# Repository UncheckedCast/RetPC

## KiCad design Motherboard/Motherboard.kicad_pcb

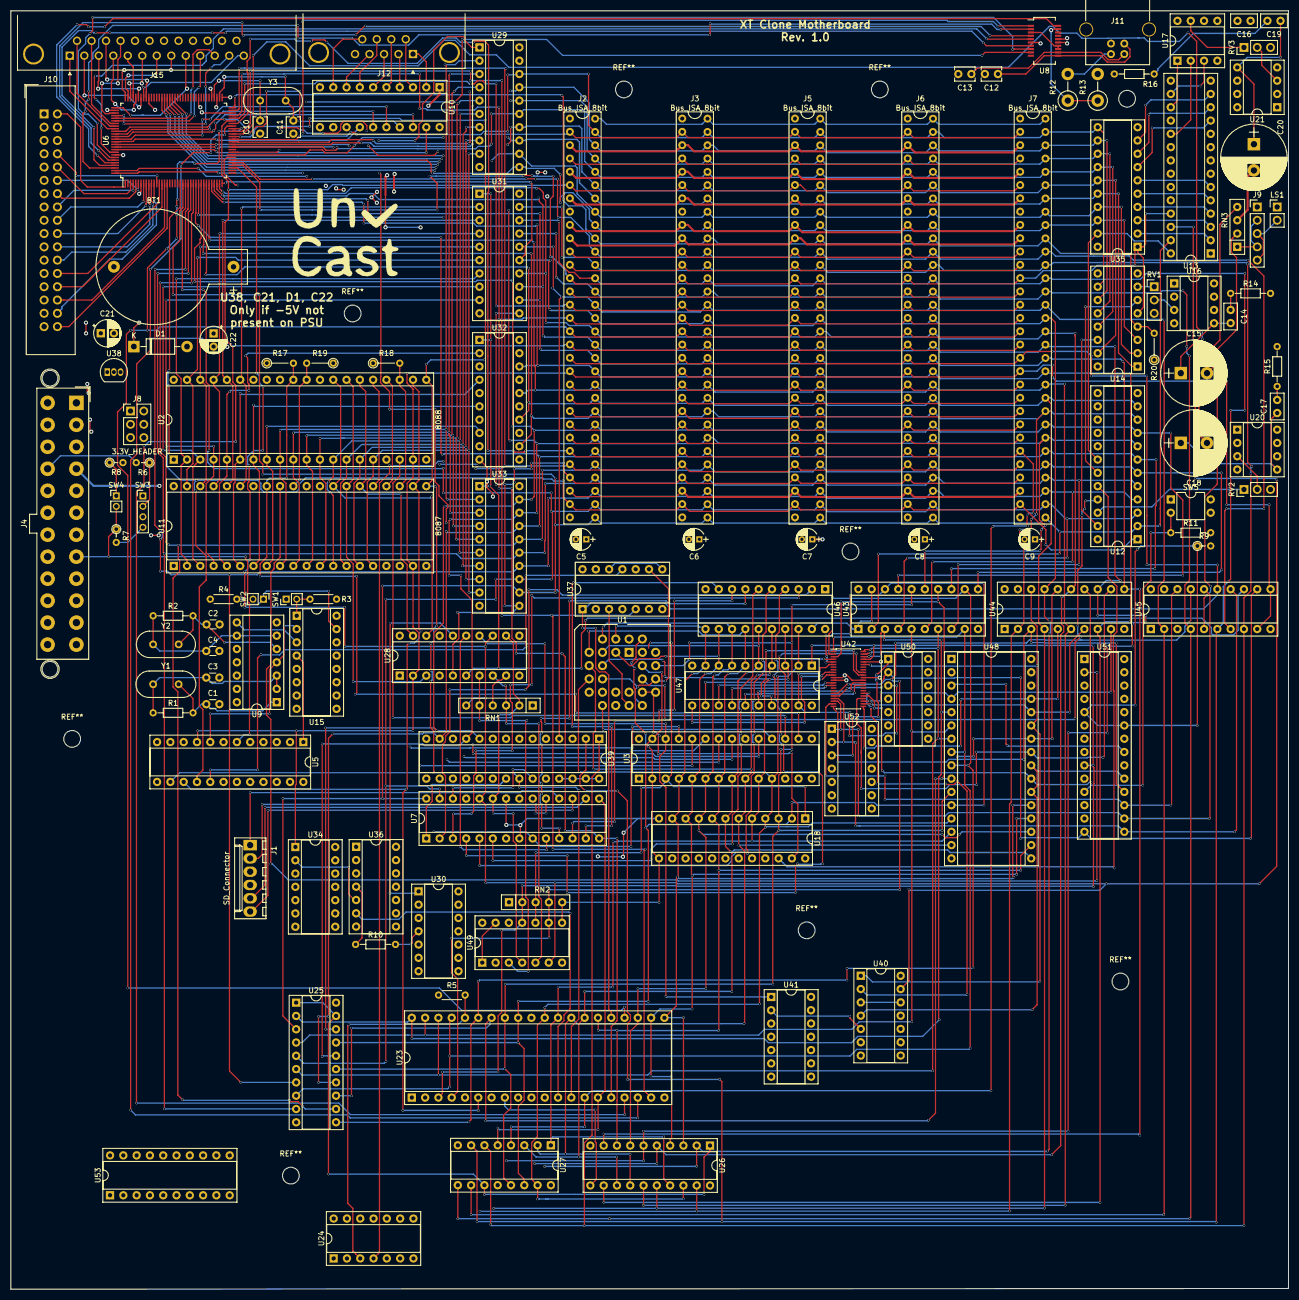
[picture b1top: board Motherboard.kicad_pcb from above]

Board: 4 copper layers, 244.1 x 244.2 mm, 122 parts (0 on the bottom side), 289 nets.

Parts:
BT1: Battery_Cell; CR2032H
C1, C3: 33p; C_Disc_D3.0mm_W1.6mm_P2.50mm
C2, C4: 30p; C_Disc_D3.0mm_W1.6mm_P2.50mm
C5, C6, C7, C8, C9: 1u; CP_Radial_D4.0mm_P2.00mm
C10, C11, C12, C13: C_Small; C_Disc_D3.8mm_W2.6mm_P2.50mm
C14, C17, C19: 50n; C_Disc_D5.0mm_W2.5mm_P2.50mm
C15, C18, C20: 270u; CP_Radial_D12.5mm_P5.00mm
C16: 100n; C_Disc_D5.0mm_W2.5mm_P2.50mm
C21: 22u; CP_Radial_D5.0mm_P2.50mm
C22: 10u; CP_Radial_D5.0mm_P2.50mm
D1: 1N4001; D_DO-41_SOD81_P10.16mm_Horizontal
J1: SD_Connector; Molex_KK-6410-06_06x2.54mm_Straight
J2, J3, J5, J6, J7: Bus_ISA_8bit; ISA-8-bit
J4: ATX24; Molex_MiniFit-JR-5556-24B_2x12x4.20mm_Straight
J8: 3.3V_HEADER; Pin_Header_Straight_2x03_Pitch2.54mm
J9: AudioJack3_SwitchTR; Pin_Header_Straight_1x05_Pitch2.54mm
J10: Conn_02x17_Odd_Even; IDC-Header_2x17_P2.54mm_Vertical
J11: USB_B
J12: DB9_Male; DSUB-9_Male_Horizontal_Pitch2.77x2.84mm_EdgePinOffset4.94mm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
J15: DB25_Female; DSUB-25_Female_Horizontal_Pitch2.77x2.84mm_EdgePinOffset4.9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
LS1: Speaker; Pin_Header_Straight_1x02_Pitch2.54mm
R1, R2: 1M; R_Axial_DIN0204_L3.6mm_D1.6mm_P7.62mm_Horizontal
R3, R4: 10k; R_Axial_DIN0204_L3.6mm_D1.6mm_P5.08mm_Horizontal
R5: 1k; R_Axial_DIN0204_L3.6mm_D1.6mm_P5.08mm_Horizontal
R6, R8, R9: 1k; R_Axial_DIN0204_L3.6mm_D1.6mm_P2.54mm_Vertical
R7: 220; R_Axial_DIN0204_L3.6mm_D1.6mm_P2.54mm_Vertical
R10: 470R; R_Axial_DIN0204_L3.6mm_D1.6mm_P7.62mm_Horizontal
R11: 6k2; R_Axial_DIN0204_L3.6mm_D1.6mm_P7.62mm_Horizontal
R12, R13: R_Small; R_Axial_DIN0411_L9.9mm_D3.6mm_P5.08mm_Vertical
R14, R15, R16: 10; R_Axial_DIN0204_L3.6mm_D1.6mm_P7.62mm_Horizontal
R17, R18, R19: 4k7; R_Axial_DIN0204_L3.6mm_D1.6mm_P5.08mm_Vertical
R20: R_Small; R_Axial_DIN0204_L3.6mm_D1.6mm_P5.08mm_Vertical
RN1: 4.7k; R_Array_SIP6
RN2: 4.7k; R_Array_SIP5
RN3: 470R; R_Array_SIP4
RV1, RV2, RV3: 10k; Pin_Header_Straight_1x03_Pitch2.54mm
SW1: TURBO; Pin_Header_Straight_1x02_Pitch2.00mm
SW2: FREEZE; Pin_Header_Straight_1x02_Pitch2.00mm
SW3: SW_SPST_LED; Pin_Header_Straight_1x04_Pitch2.00mm
SW4: RESET; Pin_Header_Straight_1x02_Pitch2.00mm
SW5: SW_DIP_x01; DIP-4_W7.62mm
U1: 82C54_PLCC; PLCC-28_THT-Socket
U2: 8088; DIP-40_W15.24mm_Socket
U3: 8259; DIP-28_W7.62mm_Socket
U5: ATF750LVC; DIP-24_W7.62mm_Socket
U6: FDC37B787-NS; LQFP-128_14x20mm_Pitch0.5mm
U7, U13: ATmega328-PU; DIP-28_W7.62mm_Socket
U8: FT231XS; SSOP-24_3.9x8.7mm_Pitch0.635mm
U9: 40106; DIP-14_W7.62mm_Socket
U10: GD75232N; DIP-20_W7.62mm_Socket
U11: 8087; DIP-40_W15.24mm_Socket
U12, U18: ATF750LVC-fdc; DIP-24_W7.62mm_Socket
U14: SN76489A-ALT; DIP-16_W7.62mm_Socket
U15: 74LS257; DIP-16_W7.62mm_Socket
U16, U20, U21: LM386; DIP-8_W7.62mm_Socket
U17: MAX538BEPA+; DIP-8_W7.62mm_Socket
U23: 8237; DIP-40_W15.24mm_Socket
U24, U30, U34, U41: 74LS04; DIP-14_W7.62mm_Socket
U25, U32, U43, U44, U45: 74LS244; DIP-20_W7.62mm_Socket
U26: 74LS373; DIP-20_W7.62mm_Socket
U27: 74LS670; DIP-16_W7.62mm_Socket
U28: 8288; DIP-20_W7.62mm_Socket
U29, U35, U46, U47: 74LS245; DIP-20_W7.62mm_Socket
U31, U33: 74LS573; DIP-20_W7.62mm_Socket
U36: 74LS00; DIP-14_W7.62mm_Socket
U37: 74LS74; DIP-14_W7.62mm_Socket
U38: L79L05_TO92; TO-92_Inline
U39, U51: ATF750LVC; DIP-28_W7.62mm_Socket
U40: 74LS27; DIP-14_W7.62mm_Socket
U42: AS6C8008; TSSOP-44_4.4x11.2mm_P0.5mm
U48: SST39SF010; DIP-32_W15.24mm_Socket
U49: 74LS243; DIP-14_W7.62mm_Socket
U50: 7400; DIP-14_W7.62mm_Socket
U52: 74LS32; DIP-14_W7.62mm_Socket
U53: 74LS322; DIP-20_W7.62mm_Socket
Y1: 14.31818 MHz; Crystal_HC49-4H_Vertical
Y2: 24.000 MHz; Crystal_HC49-U_Vertical
Y3: 32.768kHz; Crystal_HC49-U_Vertical

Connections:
+3V3: J4.1, J4.2, J4.12, J4.13, J8.2, J8.4, J8.6, U17.6
+5V: C5.1, C6.1, C7.1, C8.1, C9.1, C16.2, J1.3, J2.3, J2.29, J3.3, J3.29, J4.4, J4.6, J4.21, J4.22, J4.23, J5.3, J5.29, J6.3, J6.29, J7.3, J7.29, R3.1, R4.1, R5.1, R9.2, R11.2, R17.1, R18.1, R19.1, R20.1, RN1.1, RN2.1, U1.13, U1.17, U1.28, U2.40, U3.28, U5.5, U5.24, U6.62, U6.93, U6.121, U7.7, U7.20, U7.21, U8.15, U9.14, U10.20, U11.34, U11.40, U12.24, U13.7, U13.20, U13.21, U14.16, U15.16, U16.6, U17.8, U18.24, U20.6, U21.6, U23.5, U23.31, U25.20, U26.20, U27.16, U28.20, U29.20, U35.20, U37.2, U37.4, U37.10, U37.14, U39.24, U42.11, U42.33, U42.40, U43.20, U47.20, U48.32, U49.14, U51.24
+12V: J2.9, J3.9, J4.10, J4.11, J5.9, J6.9, J7.9, U10.1
-5V: C22.2, D1.2, J2.5, J3.5, J4.20, J5.5, J6.5, J7.5, U38.3
-12V: C21.2, D1.1, J2.7, J3.7, J4.14, J5.7, J6.7, J7.7, U10.10, U38.2
/5V_SB: J4.9, U6.69
/AD0: U2.16, U11.16, U29.9, U33.9
/AD1: U2.15, U11.15, U29.8, U33.8
/AD2: U2.14, U11.14, U29.7, U33.7
/AD3: U2.13, U11.13, U29.6, U33.6
/AD4: U2.12, U11.12, U29.5, U33.5
/AD5: U2.11, U11.11, U29.4, U33.4
/AD6: U2.10, U11.10, U29.3, U33.3
/AD7: U2.9, U11.9, U29.2, U33.2
/AD8: U2.8, U11.8, U32.8
/AD9: U2.7, U11.7, U32.6
/AD10: U2.6, U11.6, U32.4
/AD11: U2.5, U11.5, U32.2
/AD12: U2.4, U11.4, U31.9
/AD13: U2.3, U11.3, U31.8
/AD14: U2.2, U11.2, U31.7
/AD15: U2.39, U11.39, U31.6
/AD16: U2.38, U11.38, U31.5
/AD17: U2.37, U11.37, U31.4
/AD18: U2.36, U11.36, U31.3
/AD19: U2.35, U11.35, U31.2
/AEN: J2.42, J3.42, J5.42, J6.42, J7.42, U6.43, U45.7
/ALE: J2.28, J3.28, J5.28, J6.28, J7.28, U28.5, U31.11, U33.11
/BSY: R18.2, U2.23, U11.23
/DCLK: U23.12, U36.6
/DMA/A0: J2.62, J3.62, J5.62, J6.62, J7.62, U6.23, U7.28, U12.2, U13.27, U25.3, U33.12, U43.2
/DMA/A1: J2.61, J3.61, J5.61, J6.61, J7.61, U6.24, U7.27, U12.3, U25.5, U33.13, U43.4
/DMA/A2: J2.60, J3.60, J5.60, J6.60, J7.60, U6.25, U12.4, U25.7, U33.14, U43.6
/DMA/A3: J2.59, J3.59, J5.59, J6.59, J7.59, U6.26, U12.5, U25.9, U33.15, U43.8
/DMA/A4: J2.58, J3.58, J5.58, J6.58, J7.58, U6.27, U12.6, U25.12, U33.16, U43.11
/DMA/A5: J2.57, J3.57, J5.57, J6.57, J7.57, U6.28, U12.7, U25.14, U33.17, U39.13, U43.13
/DMA/A6: J2.56, J3.56, J5.56, J6.56, J7.56, U6.29, U12.8, U25.16, U33.18, U39.11, U43.15
/DMA/A7: J2.55, J3.55, J5.55, J6.55, J7.55, U6.30, U12.9, U25.18, U33.19, U39.10, U43.17
/DMA/A8: J2.54, J3.54, J5.54, J6.54, J7.54, U6.31, U12.10, U26.19, U32.12, U39.9, U44.2
/DMA/A9: J2.53, J3.53, J5.53, J6.53, J7.53, U6.32, U12.11, U26.16, U32.14, U39.8, U44.4
/DMA/A10: J2.52, J3.52, J5.52, J6.52, J7.52, U6.33, U26.15, U32.16, U44.6
/DMA/A11: J2.51, J3.51, J5.51, J6.51, J7.51, U6.34, U26.12, U32.18, U44.8
/DMA/A12: J2.50, J3.50, J5.50, J6.50, J7.50, U6.35, U26.9, U31.12, U44.11
/DMA/A13: J2.49, J3.49, J5.49, J6.49, J7.49, U6.36, U26.6, U31.13, U39.7, U44.13
/DMA/A14: J2.48, J3.48, J5.48, J6.48, J7.48, U6.37, U26.5, U31.14, U39.6, U44.15
/DMA/A15: J2.47, J3.47, J5.47, J6.47, J7.47, U6.38, U26.2, U31.15, U39.5, U44.17
/DMA/A16: J2.46, J3.46, J5.46, J6.46, J7.46, U27.10, U31.16, U39.4, U45.2
/DMA/A17: J2.45, J3.45, J5.45, J6.45, J7.45, U27.9, U31.17, U39.3, U45.4
/DMA/A18: J2.44, J3.44, J5.44, J6.44, J7.44, U27.7, U31.18, U39.2, U45.6
/DMA/A19: J2.43, J3.43, J5.43, J6.43, J7.43, U27.6, U31.19, U39.1, U45.8
/DMA/XA2: U23.34, U25.13, U42.3, U43.14, U48.10
/DMA/XA3: U23.35, U25.11, U42.2, U43.12, U48.9
/DMA/XA4: U23.37, U25.8, U42.1, U43.9, U48.8
/DMA/~DMAEN: U25.1, U25.19, U26.1, U27.11
/DRQ0: U6.55, U23.19, U37.5
/DRQ1: J2.18, J3.18, J5.18, J6.18, J7.18, U6.57, U23.18
/DRQ2: J2.6, J3.6, U6.59, U23.17
/DRQ3: J2.16, J3.16, J5.16, J6.16, J7.16, U6.61, U7.14, U23.16
/Divisible Clock/OSC_INT: U5.8, U9.4, U15.2
/Divisible Clock/~RES: J4.8, R7.1, SW4.2, U5.6
/FDC-Serial/D0: J2.40, J3.40, J5.40, J6.40, J7.40, U6.44, U7.2, U14.3, U29.11, U35.18, U46.2
/FDC-Serial/D1: J2.39, J3.39, J5.39, J6.39, J7.39, U6.45, U7.3, U14.2, U29.12, U35.17, U46.3
/FDC-Serial/D2: J2.38, J3.38, J5.38, J6.38, J7.38, U6.46, U7.4, U14.1, U29.13, U35.16, U46.4
/FDC-Serial/D3: J2.37, J3.37, J5.37, J6.37, J7.37, U6.47, U7.5, U14.15, U29.14, U35.15, U46.5
/FDC-Serial/D4: J2.36, J3.36, J5.36, J6.36, J7.36, U6.49, U7.6, U14.13, U29.15, U35.14, U46.6
/FDC-Serial/D5: J2.35, J3.35, J5.35, J6.35, J7.35, U6.50, U7.11, U14.12, U29.16, U35.13, U46.7
/FDC-Serial/D6: J2.34, J3.34, J5.34, J6.34, J7.34, U6.51, U7.12, U14.11, U29.17, U35.12, U46.8
/FDC-Serial/D7: J2.33, J3.33, J5.33, J6.33, J7.33, U6.52, U7.13, U14.10, U29.18, U35.11, U46.9
/FDC-Serial/RX1: U6.112, U10.17
/FDC-Serial/TX1: U6.113, U10.15
/FDC-Serial/~CTS1: U6.116, U10.14
/FDC-Serial/~DCD1: U6.119, U10.19
/FDC-Serial/~DSR1: U6.114, U10.18
/FDC-Serial/~DTR1: U6.117, U10.13
/FDC-Serial/~RI1: U6.118, U10.12
/FDC-Serial/~RTS1: U6.115, U10.16
/HDD Controller/ADDR: U7.26, U39.23
/HDD Controller/MISO: J1.1, U7.18
/HDD Controller/MOSI: J1.6, U7.17
/HDD Controller/SCK: J1.2, U7.19
/HDD Controller/SS-CS: J1.5, U7.16
/HDD Controller/~RESET: U7.1, U39.21
/HLDA: R19.2, U2.30, U11.31
/INTR: U2.18, U3.17
/IO-Decoder/AENBRD: U28.6, U31.1, U32.1, U33.1, U45.13
/IO-Decoder/DT_~R: U28.4, U29.1
/IO-Decoder/IO_SigDecoder/IOCHCK_I: R9.1, U51.5
/IO-Decoder/ROMADDR: U40.4, U48.22, U48.24, U51.19
/IO-Decoder/XA10: U42.27, U44.14, U48.23
/IO-Decoder/XA11: U42.26, U44.12, U48.25
/IO-Decoder/XA12: U42.25, U44.9, U48.4
/IO-Decoder/XA13: U42.24, U44.7, U48.28
/IO-Decoder/XA14: U42.23, U44.5, U48.29
/IO-Decoder/XA15: U42.22, U44.3, U51.18
/IO-Decoder/XA16: U42.21, U45.18, U51.17
/IO-Decoder/XA17: U42.20, U45.16, U51.16, U52.1
/IO-Decoder/XA18: U42.19, U45.14, U51.15, U52.2
/IO-Decoder/XA19: U42.18, U45.12, U50.2, U51.14
/IO-Decoder/~CS6: U48.3, U51.21
/IO-Decoder/~DEN: U29.19, U30.2
/IO-Decoder/~MEMW: RN1.3, U28.8, U49.5
/IO-Decoder/~MWTC: RN1.4, U28.9
/IO-Decoder/~RAMSEL: U42.6, U47.19, U50.3
/IO_READY: J2.41, J3.41, J5.41, J6.41, J7.41, R20.2, U6.64, U14.4
/IRQ0: U1.12, U3.18
/IRQ1: U3.19, U6.83
/IRQ3: U3.21, U6.84
/IRQ4: U3.22, U6.85
/IRQ5: U3.23, U6.86, U7.9
/IRQ6: U3.24, U6.87
/IRQ7: U3.25, U6.88
/ISA/IOCHCK: J2.32, J3.32, J5.32, J6.32, J7.32
/ISA/IRQ2: J2.4, J3.4
/ISA/IRQ3: J2.25, J3.25, J5.25, J6.25, J7.25
/ISA/IRQ4: J2.24, J3.24, J5.24, J6.24, J7.24
/ISA/IRQ5: J2.23, J3.23, J5.23, J6.23, J7.23
/ISA/IRQ6: J2.22, J3.22, J5.22, J6.22, J7.22
/ISA/IRQ7: J2.21, J3.21, J5.21, J6.21, J7.21
/ISA/~IOR: J2.14, J3.14, J5.14, J6.14, J7.14
/MIDI/DACCS: U13.16, U17.3
/MIDI/DIN: U13.17, U17.1
/MIDI/MIDIS_OUT: C20.2, RN3.3
/MIDI/SCLK: U13.19, U17.2
/MIDI/SPEAKER: RV2.1, U12.22
/MIDI/SPKR: C18.2, RN3.4
/MIDI/TANDY: C15.2, RN3.2
/MIDI/~PORT33X: U12.18, U13.28, U35.19
/MIDI/~TANDY_SEL: U12.19, U14.6
/MIDI/~~4MHZ: U12.23, U14.14
/N.P.NPI: U11.32, U51.2
/OSC: J2.30, J3.30, J5.30, J6.30, J7.30, U5.16, U6.22, U12.1
/PCLK: U5.17, U37.11
/PU: R17.2, U2.31, U3.16, U11.33
/QS0: U2.25, U11.25
/QS1: U2.24, U11.24
/READY: U2.22, U5.15, U11.22, U23.6
/RESET: J2.2, J3.2, J5.2, J6.2, J7.2, U2.21, U5.14, U6.53, U11.21, U23.13, U39.22
/SPEAKER: U1.20, U12.21
/SPKR_DATA: U12.20, U18.22
/SYS_CLK: J2.20, J3.20, J5.20, J6.20, J7.20, U2.19, U5.9, U11.19, U28.2, U34.1, U45.9, U45.11
/TC: J2.27, J3.27, J5.27, J6.27, J7.27, U6.63, U24.4
/XA0: U1.22, U3.27, U18.2, U23.32, U25.17, U27.14, U42.5, U43.18, U48.12
/XA1: U1.23, U18.3, U23.33, U25.15, U27.13, U42.4, U43.16, U48.11
/XA5: U23.38, U25.6, U42.44, U43.7, U48.7
/XA6: U23.39, U25.4, U42.43, U43.5, U48.6
/XA7: U23.40, U25.2, U42.42, U43.3, U48.5
/XA8: U40.1, U42.39, U44.18, U48.27
/XA9: U40.2, U42.28, U44.16, U48.26
/XD0: U1.9, U3.11, U18.4, U23.30, U26.18, U27.15, U46.18, U47.2, U48.13
/XD1: U1.8, U3.10, U18.5, U23.29, U26.17, U27.1, U46.17, U47.3, U48.14
/XD2: U1.7, U3.9, U18.6, U23.28, U26.14, U27.2, U46.16, U47.4, U48.15
/XD3: U1.6, U3.8, U18.7, U23.27, U26.13, U27.3, U46.15, U47.5, U48.17
/XD4: U1.5, U3.7, U18.8, U23.26, U26.8, U46.14, U47.6, U48.18
/XD5: U1.4, U3.6, U18.9, U23.23, U26.7, U46.13, U47.7, U48.19
/XD6: U1.3, U3.5, U18.10, U23.22, U26.4, U46.12, U47.8, U48.20
/XD7: U1.2, U3.4, U18.11, U23.21, U26.3, U46.11, U47.9, U48.21
/~AEN: U7.10, U28.15
/~DACK0: U6.54, U45.5
/~DACK0BRD: J2.19, J3.19, J5.19, J6.19, J7.19, U23.25, U37.1, U45.15
/~DACK1: J2.17, J3.17, J5.17, J6.17, J7.17, U6.56, U23.24
/~DACK2: J2.26, J3.26, J5.26, J6.26, J7.26, U6.58, U23.14, U27.4
/~DACK3: J2.15, J3.15, J5.15, J6.15, J7.15, U6.60, U7.15, U23.15, U27.5
/~DMAEN: U49.1, U49.13
/~INTA: U3.26, U28.14, U41.1
/~IOR: RN1.6, U6.41, U7.24, U13.26, U28.13, U40.13, U49.6
/~IOW: J2.13, J3.13, J5.13, J6.13, J7.13, RN1.2, U6.42, U7.23, U13.25, U14.5, U28.12, U35.1, U49.4
/~MEMR: J2.12, J3.12, J5.12, J6.12, J7.12, RN1.5, U28.7, U49.3
/~MEMW: J2.11, J3.11, J5.11, J6.11, J7.11
/~S0: U2.26, U11.26, U28.19
/~S1: U2.27, U11.27, U28.3
/~S2: U2.28, U11.28, U28.18
/~XIOR: RN2.5, U1.26, U3.2, U18.13, U49.8
/~XIOW: RN2.3, U1.27, U3.3, U18.1, U49.10
/~XMEMR: RN2.2, U23.3, U42.41, U47.1, U49.11, U51.9
/~XMEMW: RN2.4, U23.4, U42.17, U45.17, U49.9
GND: BT1.2, C1.2, C2.2, C3.2, C4.2, C5.2, C6.2, C7.2, C8.2, C9.2, C10.1, C11.1, C12.2, C13.2, C16.1, C21.1, C22.1, J1.4, J2.1, J2.10, J2.31, J3.1, J3.10, J3.31, J4.3, J4.5, J4.7, J4.15, J4.17, J4.18, J4.19, J4.24, J5.1, J5.10, J5.31, J6.1, J6.10, J6.31, J7.1, J7.10, J7.31, J8.1, J8.3, J8.5, J9.1, J10.1, J10.3, J10.5, J10.7, J10.9, J10.11, J10.13, J10.15, J10.17, J10.19, J10.21, J10.23, J10.25, J10.27, J10.29, J10.31, J10.33, J11.4, J11.5, J12.5, J15.18, J15.19, J15.20, J15.21, J15.22, J15.23, J15.24, J15.25, LS1.1, R8.2, R13.2, R14.2, R15.2, R16.2, RV1.3, RV2.3, RV3.3, SW1.1, SW2.2, SW3.1, SW3.3, SW5.1, U1.14, U2.1, U2.20, U2.33, U3.14, U5.4, U5.7, U5.12, U6.7, U6.48, U6.67, U6.74, U6.104, U7.8, U7.22, U8.6, U8.16, U9.7, U10.11, U11.1, U11.20, U12.12, U13.8, U13.22, U14.8, U15.8, U16.2, U16.4, U17.5, U18.12, U20.2, U20.4, U21.2, U21.4, U23.20, U25.10, U26.10, U27.8, U28.1, U28.10, U29.10, U31.10, U32.10, U33.10, U35.10, U37.7, U38.1, U39.12, U42.12, U42.34, U43.10, U44.1, U44.19, U45.1, U45.19, U47.10, U48.2, U48.16, U48.31, U49.7, U51.12
unnamed: BT1.1, U6.65
unnamed: C1.1, R1.2, U9.1, Y1.2
unnamed: C2.1, R2.2, U9.5, Y2.2
unnamed: C3.1, R1.1, U9.2, U9.3, Y1.1
unnamed: C4.1, R2.1, U9.6, U9.9, Y2.1
unnamed: C10.2, U6.68, Y3.1
unnamed: C11.2, U6.66, Y3.2
unnamed: C12.1, J11.3, U8.11
unnamed: C13.1, J11.2, U8.12
unnamed: C14.1, C15.1, U16.5
unnamed: C14.2, R14.1
unnamed: C17.1, C18.1, U20.5
unnamed: C17.2, R15.1
unnamed: C19.1, C20.1, U21.5
unnamed: C19.2, R16.1
unnamed: J4.16, R6.2
unnamed: J9.2, J9.4, RN3.1
unnamed: J9.3, J9.5, LS1.2
unnamed: J10.2, U6.1
unnamed: J10.8, U6.13
unnamed: J10.10, U6.3
unnamed: J10.12, U6.6
unnamed: J10.14, U6.5
unnamed: J10.16, U6.4
unnamed: J10.18, U6.8
unnamed: J10.20, U6.9
unnamed: J10.22, U6.10
unnamed: J10.24, U6.11
unnamed: J10.26, U6.14
unnamed: J10.28, U6.15
unnamed: J10.30, U6.16
unnamed: J10.32, U6.12
unnamed: J10.34, U6.17
unnamed: J11.1, R12.2
unnamed: J12.1, U10.2
unnamed: J12.2, U10.4
unnamed: J12.3, U10.6
unnamed: J12.4, U10.8
unnamed: J12.6, U10.3
unnamed: J12.7, U10.5
unnamed: J12.8, U10.7
unnamed: J12.9, U10.9
unnamed: J15.1, U6.111
unnamed: J15.2, U6.96
unnamed: J15.3, U6.97
unnamed: J15.4, U6.98
unnamed: J15.5, U6.99
unnamed: J15.6, U6.100
unnamed: J15.7, U6.101
unnamed: J15.8, U6.102
unnamed: J15.9, U6.103
unnamed: J15.10, U6.108
unnamed: J15.11, U6.107
unnamed: J15.12, U6.106
unnamed: J15.13, U6.95
unnamed: J15.14, U6.110
unnamed: J15.15, U6.109
unnamed: J15.16, U6.94
unnamed: J15.17, U6.105
unnamed: R3.2, SW1.2, U15.1
unnamed: R4.2, SW2.1, U15.15
unnamed: R5.2, U23.36, U24.3
unnamed: R6.1, SW3.2
unnamed: R7.2, SW3.4
unnamed: R8.1, SW4.1
unnamed: R10.1, U36.4
unnamed: R10.2, U30.4
unnamed: R11.1, SW5.2, U51.11
unnamed: R12.1, R13.1, U8.19
unnamed: RV1.1, U14.7
unnamed: RV1.2, U16.3
unnamed: RV2.2, U20.3
unnamed: RV3.1, U17.7
unnamed: RV3.2, U21.3
unnamed: U1.10, U1.18, U1.21, U37.9
unnamed: U1.16, U37.3
unnamed: U1.19, U18.23
unnamed: U6.120, U8.5
unnamed: U6.122, U8.8
unnamed: U6.123, U8.4
unnamed: U6.124, U8.20
unnamed: U6.125, U8.7
unnamed: U6.126, U8.2
unnamed: U6.127, U8.9
unnamed: U6.128, U8.1
unnamed: U8.3, U8.13, U8.14
unnamed: U13.2, U35.2
unnamed: U13.3, U35.3
unnamed: U13.4, U35.4
unnamed: U13.5, U35.5
unnamed: U13.6, U35.6
unnamed: U13.11, U35.7
unnamed: U13.12, U35.8
unnamed: U13.13, U35.9
unnamed: U9.8, U15.3
unnamed: U5.1, U15.4
unnamed: U23.8, U26.11
unnamed: U28.16, U30.1
unnamed: U34.2, U36.5
unnamed: U37.8, U37.12
unnamed: U40.5, U41.2
unnamed: U40.6, U46.1
unnamed: U40.3, U40.12
unnamed: U42.9, U47.11
unnamed: U42.10, U47.12
unnamed: U42.13, U47.13
unnamed: U42.14, U47.14
unnamed: U42.31, U47.15
unnamed: U42.32, U47.16
unnamed: U42.35, U47.17
unnamed: U42.36, U47.18
unnamed: U43.1, U43.19, U46.19
unnamed: U50.1, U52.3

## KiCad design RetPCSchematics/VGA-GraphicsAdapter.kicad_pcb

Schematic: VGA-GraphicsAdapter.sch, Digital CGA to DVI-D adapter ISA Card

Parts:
C1, C2, C3, C4, C5, C6, C7, C10: C; CP_Radial_D4.0mm_P1.50mm
H1, H2: MountingHole; MountingHole_2.2mm_M2
J1: Bus_ISA_8bit; 8Bit_ISA_BUS
J2: 74320-9004; DVI_Female_74320-9004; MPN 74320-9004; Digi-Key_PN WM6095-ND
J3: Conn_01x03_Male; PinHeader_1x03_P1.00mm_Vertical
R1: 220R
R2: 370R
RN1: R_Network08; R_Array_SIP9
U1: LM317T; TO-220-3; MPN LM317T; Digi-Key_PN 497-1575-5-ND
U3, U4, U6, U21: ATF22V10D; DIP-24_W7.62mm_Socket
U5, U8, U12: 74LS245; DIP-20_W7.62mm_Socket
U7, U9, U22: 74LS245A; DIP-20_W7.62mm_Socket
U10: ATmega644P-20PU; DIP-40_W15.24mm
U11: IS61LV5128AL-10TLI; TSSOP-44_4.4x11.2mm_P0.5mm
U13: SN74LVC245AN; DIP-20_W7.62mm_Socket; MPN SN74LVC245AN; Digi-Key_PN 296-8503-5-ND
U36: TFP410; HQFP-64_10x10mm_Pitch0.5mm_handsoldering
U37: ATF750C; DIP-24_W7.62mm_Socket
X1: DGOF5S3; Oscillator_DIP-14

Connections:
(inv)LE: U5.1, U8.1, U11.37 (OE(inv)), U37.21 (IO21)
+3V3: C1.2, C2.2, C3.2, C4.2, C5.2, C6.2, C7.2, C10.2, J3.2, U3.24 (VCC), U4.24 (VCC), U5.20, U6.24 (VCC), U7.20, U8.20, U9.20, U10.10 (VCC), U10.30 (AVCC), U11.11 (VDD), U11.33 (VDD), U12.20, U13.20, U21.24 (VCC), U22.20, U36.1, U36.3, U36.12, U36.15, U36.18, U36.23, U36.29, U36.33, U37.24 (VCC)
+FEMV: J1.3 (VCC), J2.14, X1.14
/A0: J1.62 (BA00), U9.2, U21.13 (IN13)
/A1: J1.61 (BA01), U9.3, U21.14 (IO14)
/A2: J1.60 (BA02), U9.4, U21.15 (IO15)
/A3: J1.59 (BA03), U9.5, U21.16 (IO16)
/A4: J1.58 (BA04), U9.6, U21.17 (IO17)
/A5: J1.57 (BA05), U9.7, U21.18 (IO18)
/A6: J1.56 (BA06), U9.8, U21.19 (IO19)
/A7: J1.55 (BA07), U9.9, U21.20 (IO20)
/A8: J1.54 (BA08), U7.2, U21.21 (IO21)
/A9: J1.53 (BA09), U7.3, U21.11 (IN11)
/A10: J1.52 (BA10), U7.4, U21.10 (IN10)
/A11: J1.51 (BA11), U7.5, U21.9 (IN9)
/A12: J1.50 (BA12), U7.6, U21.8 (IN8)
/A13: J1.49 (BA13), U7.7, U21.7 (IN7)
/A14: J1.48 (BA14), U7.8, U21.6 (IN6)
/A15: J1.47 (BA15), U7.9, U21.5 (IN5)
/D0: U11.9 (IO/0), U12.18, U13.9
/D1: U11.10 (IO/1), U12.17, U13.8
/D2: U11.13 (IO/2), U12.16, U13.7
/D3: U11.14 (IO/3), U12.15, U13.6
/D4: U11.31 (IO/4), U12.14, U13.5
/D5: U11.32 (IO/5), U12.13, U13.4
/D6: U11.36 (IO/7), U12.12, U13.3
/D7: U11.35 (IO/6), U12.11, U13.2
/VA0: U3.14 (IO14), U4.10 (IN10), U8.18, U11.3 (A0)
/VA1: U3.15 (IO15), U4.9 (IN9), U8.17, U11.4 (A1)
/VA2: U3.16 (IO16), U4.8 (IN8), U8.16, U11.5 (A2)
/VA3: U3.17 (IO17), U4.7 (IN7), U8.15, U11.6 (A3)
/VA4: U3.18 (IO18), U4.6 (IN6), U8.14, U11.7 (A4)
/VA5: U3.19 (IO19), U4.5 (IN5), U8.13, U11.16 (A5)
/VA6: U3.20 (IO20), U4.4 (PD/IN4), U8.12, U11.17 (A6)
/VA7: U3.21 (IO21), U4.3 (IN3), U8.11, U11.18 (A7)
/VA8: U3.22 (IO22), U4.2 (IN2), U5.18, U11.19 (A8)
/VA9: U3.23 (IO23), U4.1 (CLK/IN1), U5.17, U11.20 (A9)
/VA10: U4.14 (IO14), U5.16, U11.26 (A10)
/VA11: U4.15 (IO15), U5.15, U11.27 (A11)
/VA12: U4.16 (IO16), U5.14, U11.28 (A12)
/VA13: U4.17 (IO17), U5.13, U11.29 (A13)
/VA14: U4.18 (IO18), U5.12, U11.30 (A14)
/VA15: U4.19 (IO19), U5.11, U11.38 (A15)
/VA16: U4.20 (IO20), U6.18 (IO18), U11.39 (A16)
/VA17: U4.21 (IO21), U6.17 (IO17), U11.40 (A17)
/VA18: U4.22 (IO22), U6.19 (IO19), U11.41 (A18)
/XA0: U8.2, U9.18, U10.23 (PC1)
/XA1: U8.3, U9.17, U10.22 (PC0)
/XA2: U8.4, U9.16, U10.8 (PB7)
/XA3: U8.5, U9.15, U10.7 (PB6)
/XA4: U8.6, U9.14, U10.6 (PB5)
/XA5: U8.7, U9.13, U10.5 (PB4)
/XA6: U8.8, U9.12, U10.4 (PB3)
/XA7: U8.9, U9.11, U10.3 (PB2)
/XA8: U5.2, U7.18, U10.2 (PB1)
/XA9: U5.3, U7.17, U10.1 (PB0)
/XA10: U5.4, U7.16, U10.40 (PA0)
/XA11: U5.5, U7.15, U10.39 (PA1)
/XA12: U5.6, U7.14, U10.38 (PA2)
/XA13: U5.7, U7.13, U10.37 (PA3)
/XA14: U5.8, U7.12, U10.36 (PA4)
/XA15: U5.9, U7.11, U10.35 (PA5)
/XA16: U6.7 (IN7), U10.34 (PA6)
/XA17: U6.8 (IN8), U10.33 (PA7)
/XA18: U6.6 (IN6), U10.24 (PC2)
AEN: J1.42 (AEN), U37.3 (IN3)
ALEN: J1.28 (ALE), U7.1, U9.1, U37.7 (IN7)
ALEN(inv): U7.19, U9.19, U37.19 (IO19)
DE: U36.2, U37.16 (IO16)
Dir: U10.26 (PC4), U22.1
GClock: U6.14 (IO14), U36.57, U37.1 (CLK/IN1)
GEnd: U4.23 (IO23), U37.6 (IN6)
GEnd(inv): U12.19, U37.18 (IO18)
Hsync: U36.4, U37.15 (IO15)
IOR: J1.14 (~IOR), U37.4 (PD/IN4)
IOW: J1.13 (~IOW), U37.2 (IN2)
LoadEnable: U6.3 (IN3), U10.28 (PC6), U11.15 (WE(inv)), U13.19, U37.9 (IN9)
MemW: J1.11 (~MEM), U37.5 (IN5)
unnamed: J1.33 (DB7), U22.9
unnamed: J1.34 (DB6), U22.8
unnamed: J1.35 (DB5), U22.7
unnamed: J1.36 (DB4), U22.6
unnamed: J1.37 (DB3), U22.5
unnamed: J1.38 (DB2), U22.4
unnamed: J1.39 (DB1), U22.3
unnamed: J1.40 (DB0), U22.2
unnamed: J1.43 (BA19), U21.1 (CLK/IN1)
unnamed: J1.44 (BA18), U21.2 (IN2)
unnamed: J1.45 (BA17), U21.3 (IN3)
unnamed: J1.46 (BA16), U21.4 (PD/IN4)
unnamed: RN1.2, U12.2, U36.36, U36.40
unnamed: RN1.3, U12.3, U36.37, U36.41
unnamed: RN1.4, U12.4, U36.38, U36.42
unnamed: RN1.5, U12.5, U36.44, U36.50
unnamed: RN1.6, U12.6, U36.45, U36.51
unnamed: RN1.7, U12.7, U36.46, U36.52
unnamed: RN1.8, U12.8, U36.54, U36.60
unnamed: RN1.9, U12.9, U36.55, U36.61
unnamed: U3.1 (CLK/IN1), U6.16 (IO16)
unnamed: U6.1 (CLK/IN1), X1.8
unnamed: U10.14 (PD0), U13.11, U22.18
unnamed: U10.15 (PD1), U13.12, U22.17
unnamed: U10.16 (PD2), U13.13, U22.16
unnamed: U10.17 (PD3), U13.14, U22.15
unnamed: U10.18 (PD4), U13.15, U22.14
unnamed: U10.19 (PD5), U13.16, U22.13
unnamed: U10.20 (PD6), U13.17, U22.12
unnamed: U10.21 (PD7), U13.18, U22.11
OP: U6.2 (IN2), U10.27 (PC5)
RST: J1.2 (RESET), U37.8 (IN8)
RST(inv): U10.9 (~RESET), U37.20 (IO20)
Sel: U10.25 (PC3), U21.23 (IO23), U22.19
TX0+: J2.18, U36.25
TX0-: J2.17, U36.24
TX1+: J2.10, U36.28
TX1-: J2.9, U36.27
TX2+: J2.2, U36.31
TX2-: J2.1, U36.30
TXC+: J2.23, U36.22
TXC-: J2.24, U36.21
Vsync: U36.5, U37.14 (IO14)
busr: U10.29 (PC7), U37.17 (IO17)

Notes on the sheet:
~~3.35V

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
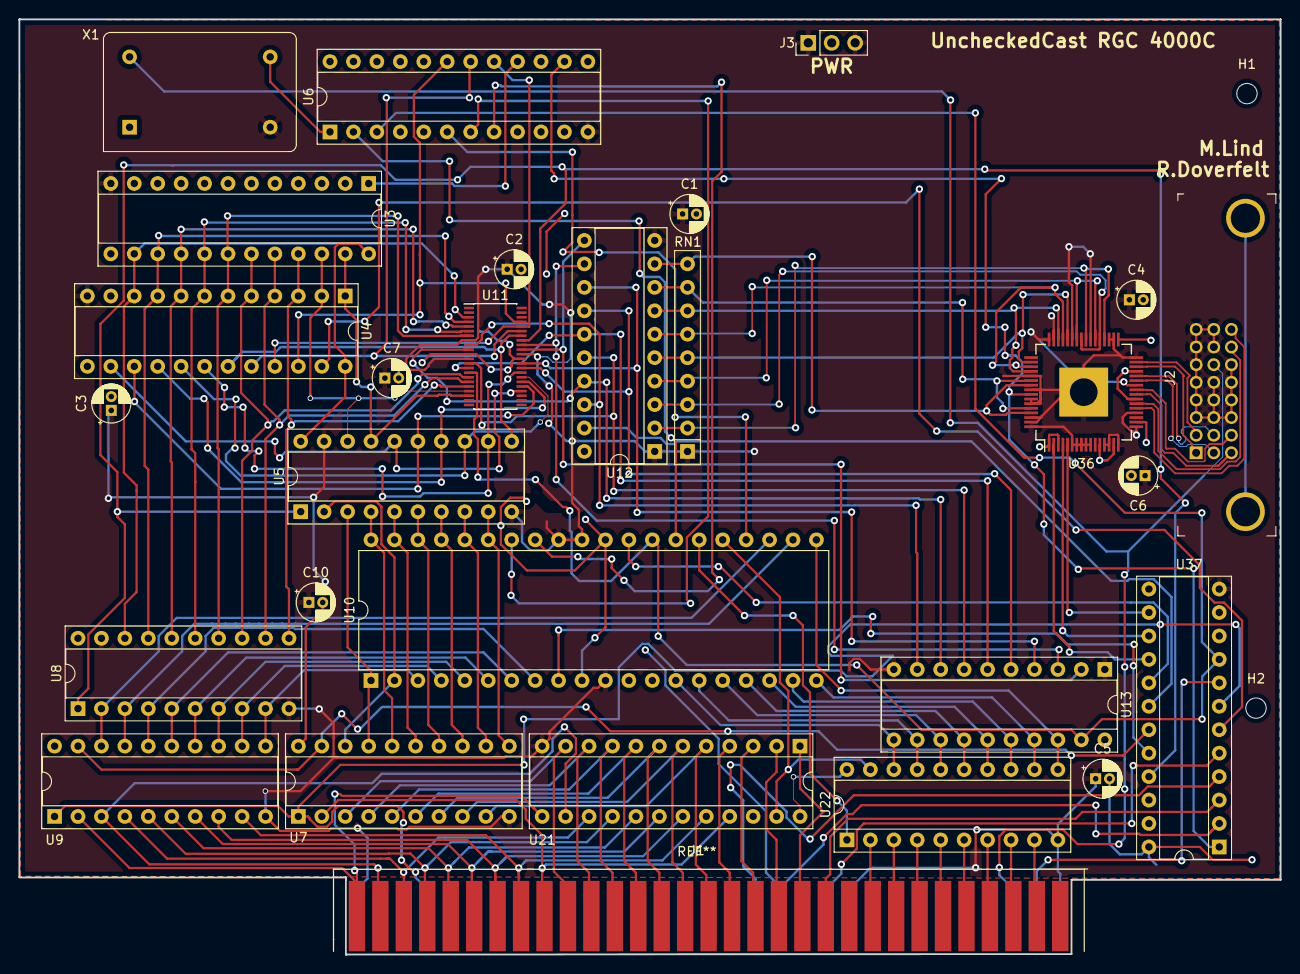
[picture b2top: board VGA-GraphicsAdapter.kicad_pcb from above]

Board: 2 copper layers, 136.7 x 101.3 mm, 30 parts (0 on the bottom side), 123 nets.

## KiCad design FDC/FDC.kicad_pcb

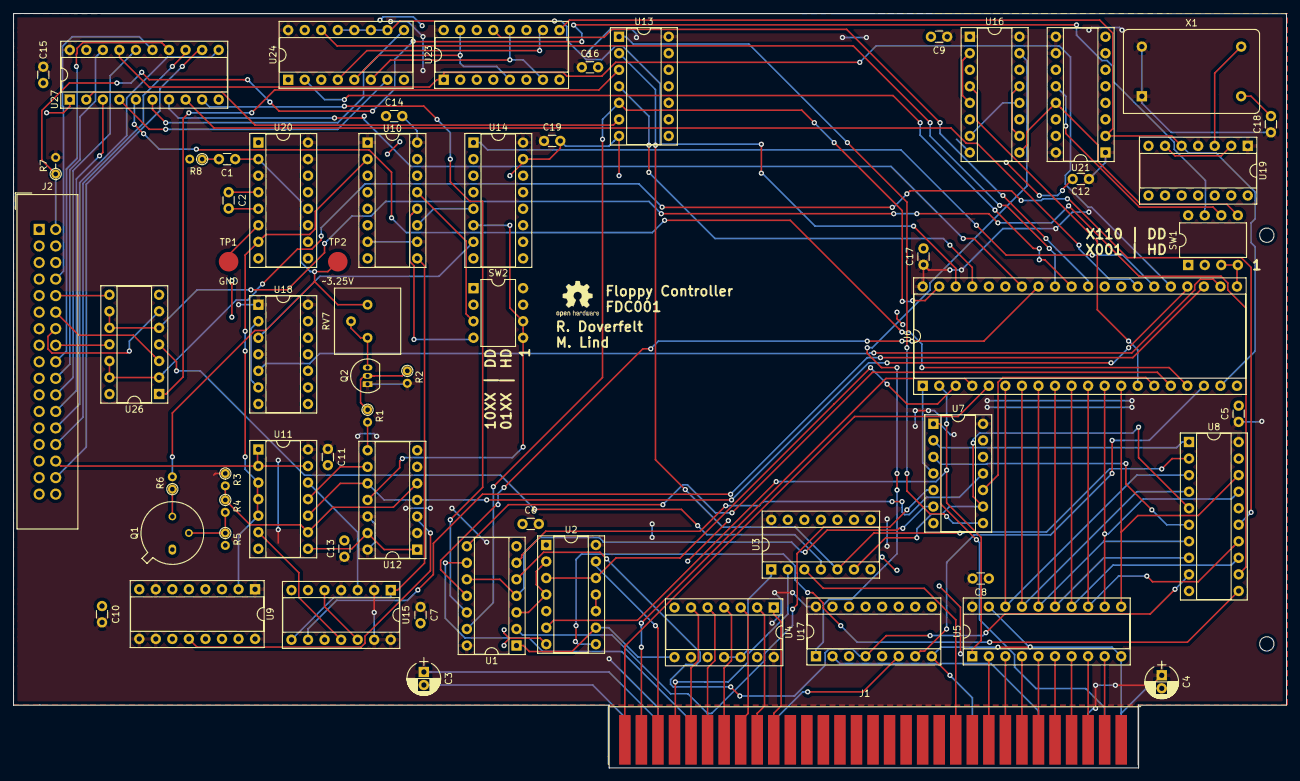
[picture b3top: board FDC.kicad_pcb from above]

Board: 2 copper layers, 195.4 x 115.8 mm, 62 parts (0 on the bottom side), 128 nets.

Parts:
C1: 100p; C_Disc_D3.0mm_W1.6mm_P2.50mm
C2: 33p; C_Disc_D3.0mm_W1.6mm_P2.50mm
C3, C4: 8u2; CP_Radial_D5.0mm_P2.00mm
C5, C6, C7, C8, C9, C10, C11, C12, C13, C14, C15, C16, C17, C18, C19: 4n7; C_Disc_D3.0mm_W1.6mm_P2.50mm
J1: Bus_ISA_8bit; 8Bit_ISA_BUS
J2: Floppy IDC; IDC-Header_2x17_P2.54mm_Vertical
Q1: 2N2219; TO-39-3
Q2: 2N3905; TO-92_Inline_Narrow_Oval
R1: 2k2; R_Axial_DIN0204_L3.6mm_D1.6mm_P1.90mm_Vertical
R2, R3, R5: 1k; R_Axial_DIN0204_L3.6mm_D1.6mm_P1.90mm_Vertical
R4: 1k5; R_Axial_DIN0204_L3.6mm_D1.6mm_P1.90mm_Vertical
R6: 33k; R_Axial_DIN0204_L3.6mm_D1.6mm_P1.90mm_Vertical
R7: 4k7; R_Axial_DIN0204_L3.6mm_D1.6mm_P2.54mm_Vertical
R8: 330R; R_Axial_DIN0204_L3.6mm_D1.6mm_P1.90mm_Vertical
RV7: 20k; 3386P
SW1, SW2: DSEL; DIP-8_W7.62mm
TP1: GND; Measurement_Point_Round-SMD-Pad_Big
TP2: ~~3.25V; Measurement_Point_Round-SMD-Pad_Big
U1, U13: 74LS08; DIP-14_W7.62mm_Socket
U2: 74LS32; DIP-14_W7.62mm_Socket
U3: 74LS02; DIP-14_W7.62mm_Socket
U4: 74LS30; DIP-14_W7.62mm_Socket
U5: 74LS245; DIP-20_W7.62mm_Socket
U6: uPD765BC; DIP-40_W15.24mm_Socket
U7: 74LS04; DIP-14_W7.62mm_Socket
U8: 74LS273; DIP-20_W7.62mm_Socket
U9, U10, U21: 74LS161; DIP-16_W7.62mm_Socket
U11: 74LS10; DIP-14_W7.62mm_Socket
U12, U15, U18, U19: 74LS74; DIP-14_W7.62mm_Socket
U14: 74LS157; DIP-16_W7.62mm_Socket
U16, U23: 74LS175; DIP-16_W7.62mm_Socket
U17: MC3487N; DIP-16_W7.62mm_Socket
U20: 74LS629; DIP-16_W7.62mm_Socket
U24: 74LS153; DIP-16_W7.62mm_Socket
U26: 74LS38; DIP-14_W7.62mm_Socket
U27: 74HC240; DIP-20_W7.62mm_Socket
X1: 16MHZ; Oscillator_DIP-14

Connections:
+5V: C3.1, C4.1, C5.1, C6.2, C7.1, C8.2, C9.1, C10.2, C11.1, C12.2, C13.1, C14.2, C15.1, C16.1, C17.1, C18.1, C19.1, J1.3, J1.29, Q2.1, R2.2, R3.1, R7.2, U1.14, U2.14, U3.14, U4.14, U5.20, U6.40, U7.14, U8.20, U9.1, U9.7, U9.9, U9.10, U9.16, U10.1, U10.7, U10.10, U10.16, U11.14, U12.2, U12.12, U12.14, U13.14, U14.16, U15.2, U15.4, U15.10, U15.13, U15.14, U16.1, U16.16, U17.16, U18.1, U18.4, U18.14, U19.1, U19.4, U20.3, U20.15, U20.16, U21.1, U21.7, U21.9, U21.10, U21.16, U23.16, U24.16, U27.20, X1.1, X1.14
/1MHZ: SW1.6, U21.12
/2MHZ: SW1.5, U16.9, U21.13
/8MHZ: U6.19, U19.5, U21.2, U23.9
/A0: J1.62, U6.5
/A1: J1.61, U6.4
/A2: J1.60, U2.13
/ADDR: U1.1, U2.9, U4.8
/AEN: J1.42, U3.3
/D0: U5.18, U6.6, U8.3
/D1: U5.17, U6.7, U8.4
/D2: U5.16, U6.8, U8.7
/D3: U5.15, U6.9, U8.8
/D4: U5.14, U6.10, U8.13
/D5: U5.13, U6.11, U8.14
/D6: U5.12, U6.12, U8.17
/D7: U5.11, U6.13, U8.18
/DB0: J1.40, U5.2
/DB1: J1.39, U5.3
/DB2: J1.38, U5.4
/DB3: J1.37, U5.5
/DB4: J1.36, U5.6
/DB5: J1.35, U5.7
/DB6: J1.34, U5.8
/DB7: J1.33, U5.9
/DIRU: U24.9, U27.6
/DMA_GATE: U1.5, U8.9, U17.4
/DRQ: U6.14, U16.4
/DRQ2: J1.6, U17.2
/FR_STEP: U6.37, U13.4
/INDEX: U6.17, U27.5
/INT: U6.18, U17.7
/IRQ6: J1.22, U17.6
/LCT_DIR: U6.38, U24.10, U24.11, U24.12, U24.13
/PLL/1MHZ: SW2.4, U10.12
/PLL/2MHZ: SW2.3, U10.13
/PLL/8MHZ_NOM: U9.2, U10.2, U11.3, U11.4, U11.5, U20.7
/PLL/500KHZ: U10.11, U14.5
/PLL/DATA_WINDOW: U6.22, U18.5
/PLL/DOUT: U6.23, U15.9
/PLL/MFM: U6.26, U14.1
/PLL/PLLCLK: SW2.5, SW2.6, U12.11, U14.6
/PLL/VCO_SYNC: U6.24, U11.10, U12.4, U12.10
/PS0: U6.32, U24.14
/PS1: U6.31, U24.2
/RESET: J1.2, U7.1
/RST: U6.1, U7.4
/SEEK: U1.13, U6.39, U13.5
/SELU: U6.27, U27.8
/TC: J1.27, U1.9
/TCDACK: U1.8, U6.16
/TRK0: U1.11, U6.33
/TRK00: U1.12, U27.9
/WDATA: U6.30, U23.13
/WDATU: U24.7, U27.4
/WE: U6.25, U23.1, U27.17
/WEARLY: U23.5, U23.15, U24.5
/WLATE: U23.10, U24.4
/WNORMAL: U23.7, U23.12, U24.6
/WPT: U6.34, U27.7
/~DACK: U6.15, U7.10
/~DACK2: J1.26, U1.2, U7.5
/~DIR: J2.18, U27.14
/~DRVSA: J2.14, U26.6
/~DRVSB: J2.12, U26.3
/~INDEX: J2.8, U27.15
/~MOTEA: J2.10, U26.8
/~MOTEB: J2.16, U26.11
/~RD: U2.6, U5.1, U6.2
/~RDATA: J2.30, U11.1, U11.2, U11.13
/~REDWC: J2.2, R7.1, SW1.7
/~SIDE1: J2.32, U27.12
/~STEP: J2.20, U27.18
/~TRK00: J2.26, U27.11
/~WDATA: J2.22, U27.16
/~WGATE: J2.24, U27.3
/~WPT: J2.28, U27.13
/~WR: U2.3, U2.12, U6.3
GND: C3.2, C4.2, C5.2, C6.1, C7.2, C8.1, C9.2, C10.1, C11.2, C12.1, C13.2, C14.1, C15.2, C16.2, C17.2, C18.2, C19.2, J1.1, J1.10, J1.31, J2.1, J2.3, J2.5, J2.7, J2.9, J2.11, J2.13, J2.15, J2.17, J2.19, J2.21, J2.23, J2.25, J2.27, J2.29, J2.31, J2.33, Q1.1, R5.2, R8.2, SW1.2, TP1.1, U1.7, U2.7, U3.7, U4.7, U5.10, U5.19, U6.20, U7.7, U8.10, U9.8, U10.3, U10.4, U10.5, U10.6, U10.8, U11.7, U12.7, U13.7, U14.8, U14.15, U15.7, U16.8, U17.8, U18.7, U20.6, U20.9, U21.8, U23.8, U24.1, U24.3, U24.8, U24.15, U27.1, U27.10, U27.19, X1.7
unnamed: C1.1, R6.2, RV7.1, TP2.1, U20.2
unnamed: C1.2, R8.1
unnamed: C2.1, U20.4
unnamed: C2.2, U20.5
unnamed: J1.53, U4.1
unnamed: J1.54, U4.2
unnamed: J1.55, U4.3
unnamed: J1.56, U4.4
unnamed: J1.57, U4.5
unnamed: J1.58, U4.6
unnamed: J1.59, U3.2
unnamed: Q1.2, R4.2, R5.1
unnamed: Q1.3, R6.1
unnamed: Q2.2, R1.1, R2.1
unnamed: Q2.3, RV7.2, RV7.3
unnamed: R1.2, U12.8
unnamed: R3.2, R4.1, U11.9, U12.5
unnamed: SW1.3, SW1.4, U6.21
unnamed: U1.3, U2.2, U2.4
unnamed: U1.6, U7.11
unnamed: U1.4, U1.10, U7.6
unnamed: U2.8, U8.11
unnamed: U2.10, U2.11
unnamed: U3.1, U4.11, U4.12
unnamed: U3.6, U7.9, U8.5
unnamed: U7.2, U8.1
unnamed: U7.3, U8.6
unnamed: U10.9, U15.1, U15.8
unnamed: U11.6, U15.11
unnamed: U11.8, U12.1, U12.13
unnamed: U11.11, U12.9
unnamed: U11.12, U15.3
unnamed: U9.12, U12.3
unnamed: U7.8, U13.1
unnamed: U3.5, U8.2, U13.2
unnamed: U13.3, U26.1
unnamed: U13.6, U27.2
unnamed: U14.7, U18.3
unnamed: U15.5, U15.12
unnamed: U16.2, U16.5
unnamed: U16.10, U16.13
unnamed: U16.7, U16.12
unnamed: U16.15, U17.1
unnamed: U18.2, U18.6
unnamed: U19.2, U19.6
unnamed: U19.3, X1.8
unnamed: U3.4, U26.4
unnamed: U8.12, U26.5, U26.9, U26.10
unnamed: U8.15, U26.2, U26.12, U26.13

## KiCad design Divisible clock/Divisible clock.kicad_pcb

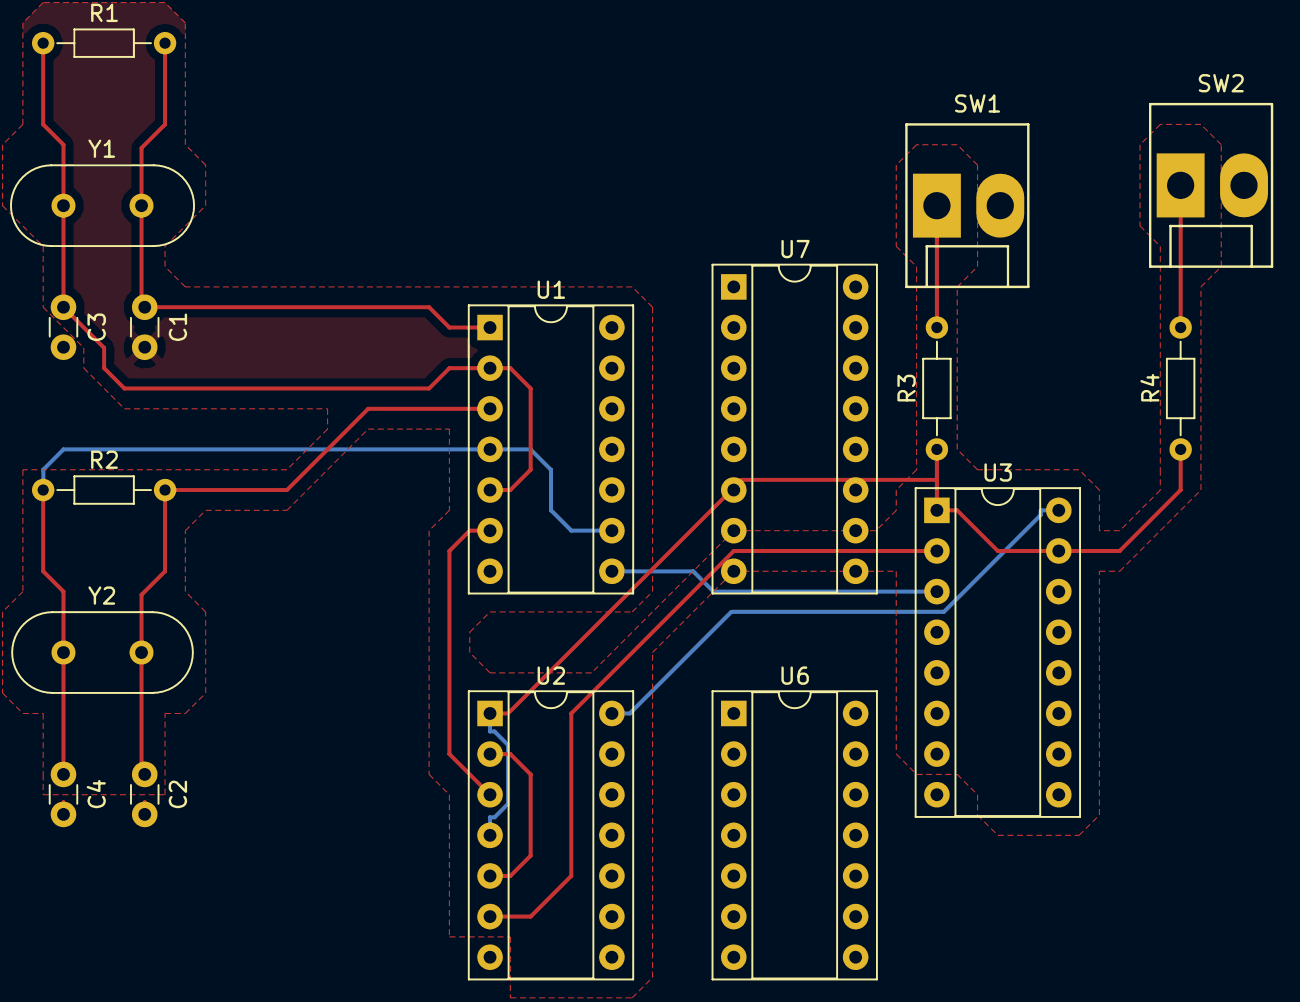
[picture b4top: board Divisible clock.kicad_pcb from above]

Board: 2 copper layers, 17 parts (0 on the bottom side), 21 nets.

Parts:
C1, C2, C3, C4: 33p; C_Disc_D3.0mm_W1.6mm_P2.50mm
R1, R2: 1M; R_Axial_DIN0204_L3.6mm_D1.6mm_P7.62mm_Horizontal
R3, R4: 10k; R_Axial_DIN0204_L3.6mm_D1.6mm_P7.62mm_Horizontal
SW1: CLK_SEL; Molex_KK-41791-02_02x3.96mm_Straight
SW2: FREEZE; Molex_KK-41791-02_02x3.96mm_Straight
U1: 4069; DIP-14_W7.62mm_Socket
U2: 40106; DIP-14_W7.62mm_Socket
U3: 4081; DIP-16_W7.62mm_Socket
U6: 74LS77; DIP-14_W7.62mm_Socket
U7: 74LS257; DIP-16_W7.62mm_Socket
Y1: 18.432 MHz; Crystal_HC49-4H_Vertical
Y2: 32.768 MHz; Crystal_HC49-U_Vertical

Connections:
+5V: R3.1, R4.1, U7.1, U7.15
GND: C1.2, C2.2, C3.2, C4.2, SW1.2, SW2.2, U6.11, U7.8
unnamed: C1.1, R1.2, U2.1, Y1.2
unnamed: C2.1, R2.2, U2.3, Y2.2
unnamed: C3.1, R1.1, U2.2, U2.5, Y1.1
unnamed: C4.1, R2.1, U2.4, U2.9, Y2.1
unnamed: R3.2, SW1.1
unnamed: R4.2, SW2.1
unnamed: U1.2, U3.2
unnamed: U1.4, U3.6
unnamed: U1.5, U3.13, U7.4
unnamed: U1.6, U1.9
unnamed: U2.6, U7.2
unnamed: U2.8, U7.3
unnamed: U3.9, U6.1
unnamed: U3.10, U6.2
SYS_CLK: U1.11, U6.12
VCC: U6.4, U7.16
VDD: U1.14, U2.14, U3.14
VSS: U1.7, U2.7, U3.7
~SYS_CLK: U1.10, U6.3
